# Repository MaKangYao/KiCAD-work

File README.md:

# KiCAD
Kicad绘制的原理图与电路板图
Schematic diagram and circuit board diagram drawn by Kicad

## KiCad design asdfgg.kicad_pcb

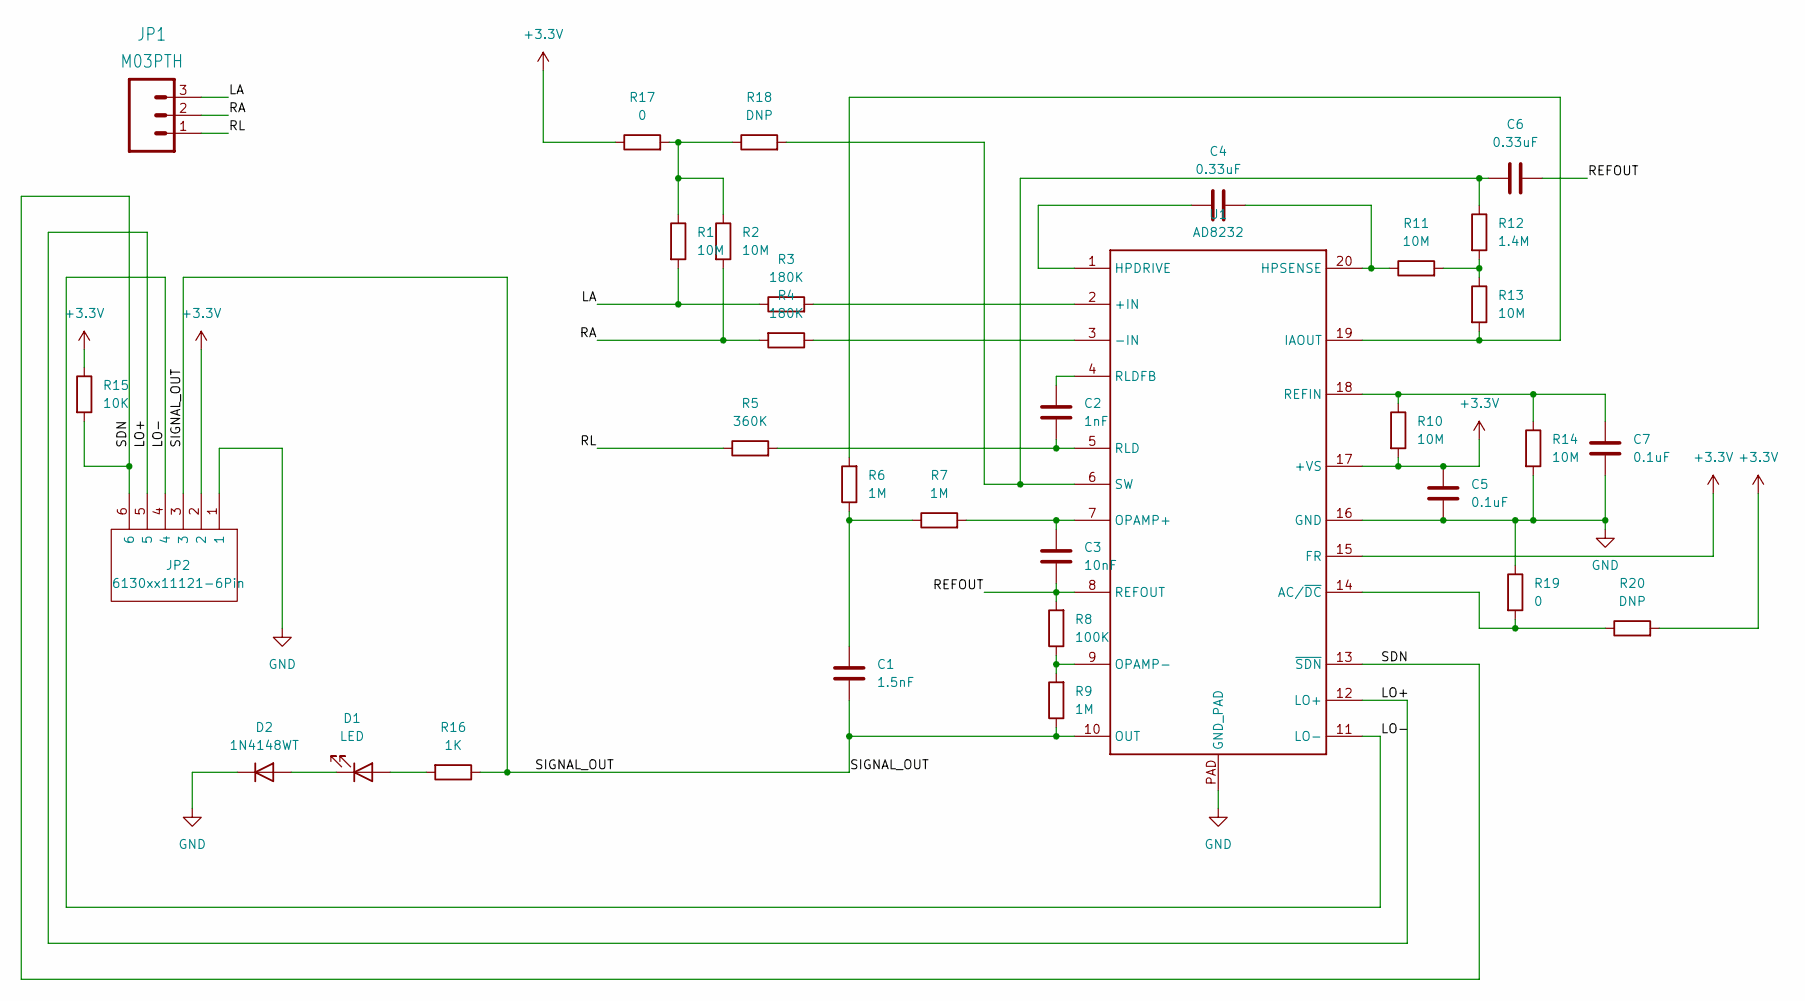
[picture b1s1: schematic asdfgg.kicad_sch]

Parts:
C1: 1.5nF; C_0603_WJQ
C2: 1nF; C_0603_WJQ
C3: 10nF; C_0603_WJQ
C4, C6: 0.33uF; C_0603_WJQ
C5, C7: 0.1uF; C_0603_WJQ
D1: LED; LED_0603_1608Metric
D2: 1N4148WT; D_SOD-523
JP1: M03PTH; Hirose_FH12-13S-0.5SH_1x13-1MP_P0.50mm_Horizontal
JP2: 6130xx11121-6Pin; HDRV6W64P0X254_1X6_1524X254X869P; Manufacturer_Part_Number 6130xx11121-6Pin
R1, R2, R10, R11, R13, R14: 10M; R_0603_WJQ
R3, R4: 180K; R_0603_WJQ
R5: 360K; R_0603_WJQ
R6, R7, R9: 1M; R_0603_WJQ
R8: 100K; R_0603_WJQ
R12: 1.4M; R_0603_WJQ
R15: 10K; R_0603_WJQ
R16: 1K; R_0603_WJQ
R17, R19: 0; R_0603_WJQ
R18, R20: DNP; R_0603_WJQ
U1: AD8232; QFN50P400X400X80-21N-D

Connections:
+3.3V: C5.1, JP2.2, R10.2, R15.1, R17.1, R20.2, U1.15 (FR), U1.17 (+VS)
/LA: JP1.3, R1.2, R3.1
/LO+: JP2.5, U1.12 (LO+)
/LO-: JP2.4, U1.11 (LO-)
/RA: JP1.2, R2.2, R4.2
/REFOUT: C3.2, C6.2, R8.2, U1.8 (REFOUT)
/RL: JP1.1, R5.1
/SDN: JP2.6, R15.2, U1.13 (~SDN)
/SIGNAL_OUT: C1.2, JP2.3, R9.1, R16.1, U1.10 (OUT)
GND: C5.2, C7.2, D2.1 (K), JP2.1, R14.2, R19.1, U1.16 (GND), U1.PAD (GND_PAD)
unnamed: C1.1, R6.1, R7.1
unnamed: C2.1, U1.4 (RLDFB)
unnamed: C2.2, R5.2, U1.5 (RLD)
unnamed: C3.1, R7.2, U1.7 (OPAMP+)
unnamed: C4.1, U1.1 (HPDRIVE)
unnamed: C4.2, R11.1, U1.20 (HPSENSE)
unnamed: C6.1, R12.1, R18.2, U1.6 (SW)
unnamed: C7.1, R10.1, R14.1, U1.18 (REFIN)
unnamed: D1.1 (K), D2.2 (A)
unnamed: D1.2 (A), R16.2
unnamed: R1.1, R2.1, R17.2, R18.1
unnamed: R3.2, U1.2 (+IN)
unnamed: R4.1, U1.3 (-IN)
unnamed: R8.1, R9.2, U1.9 (OPAMP-)
unnamed: R11.2, R12.2, R13.1
unnamed: R6.2, R13.2, U1.19 (IAOUT)
unnamed: R19.2, R20.1, U1.14 (AC/~DC)

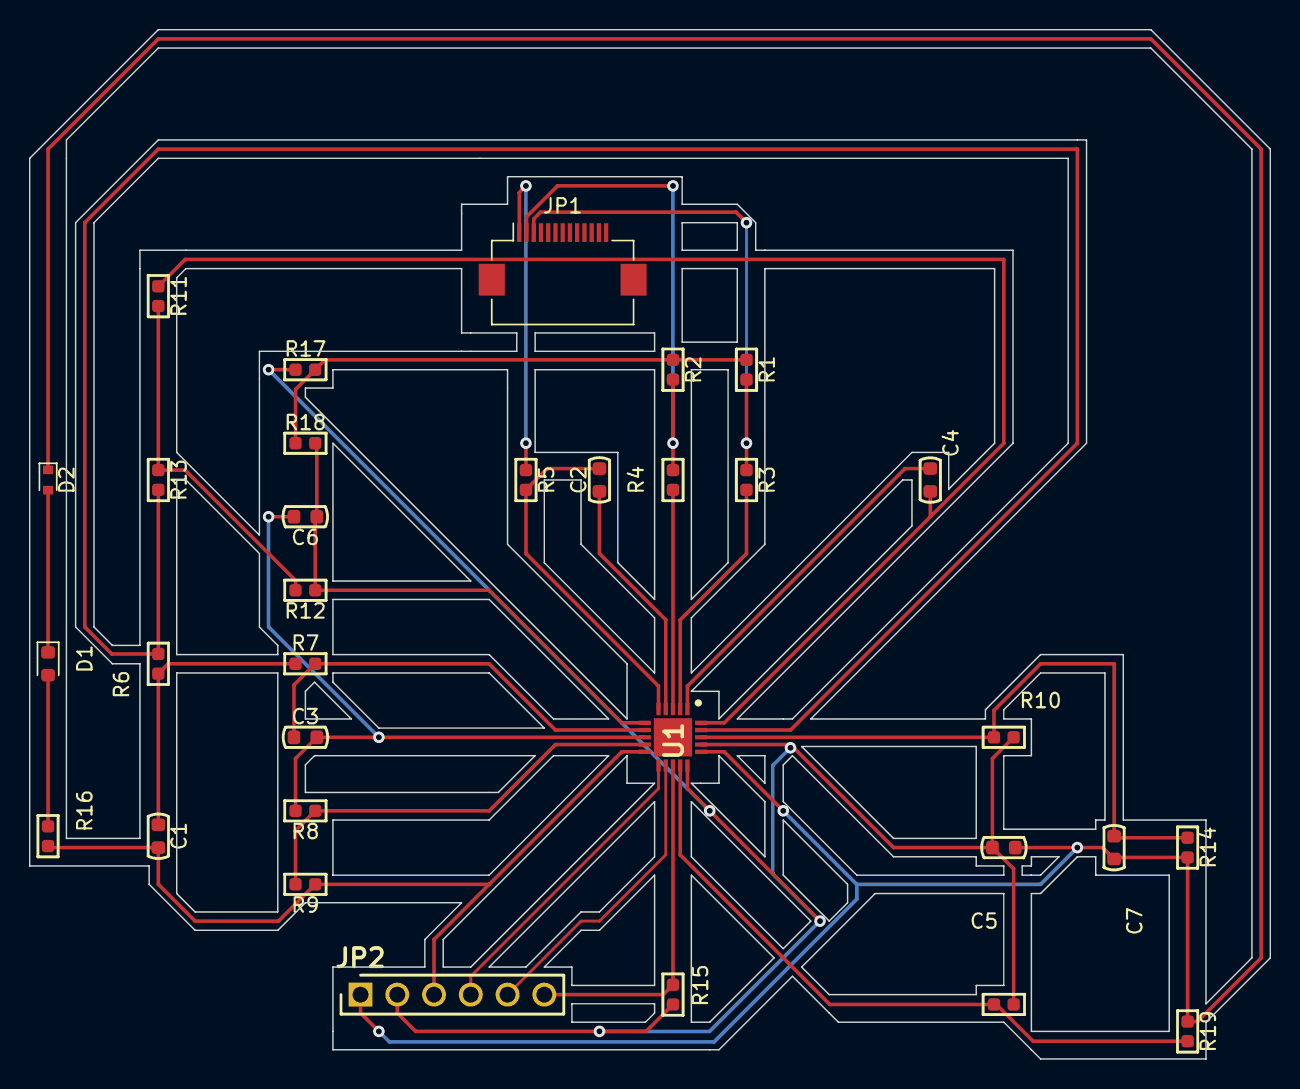
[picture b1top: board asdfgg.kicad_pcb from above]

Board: 2 copper layers, 85.7 x 71.1 mm, 32 parts (0 on the bottom side), 27 nets.
